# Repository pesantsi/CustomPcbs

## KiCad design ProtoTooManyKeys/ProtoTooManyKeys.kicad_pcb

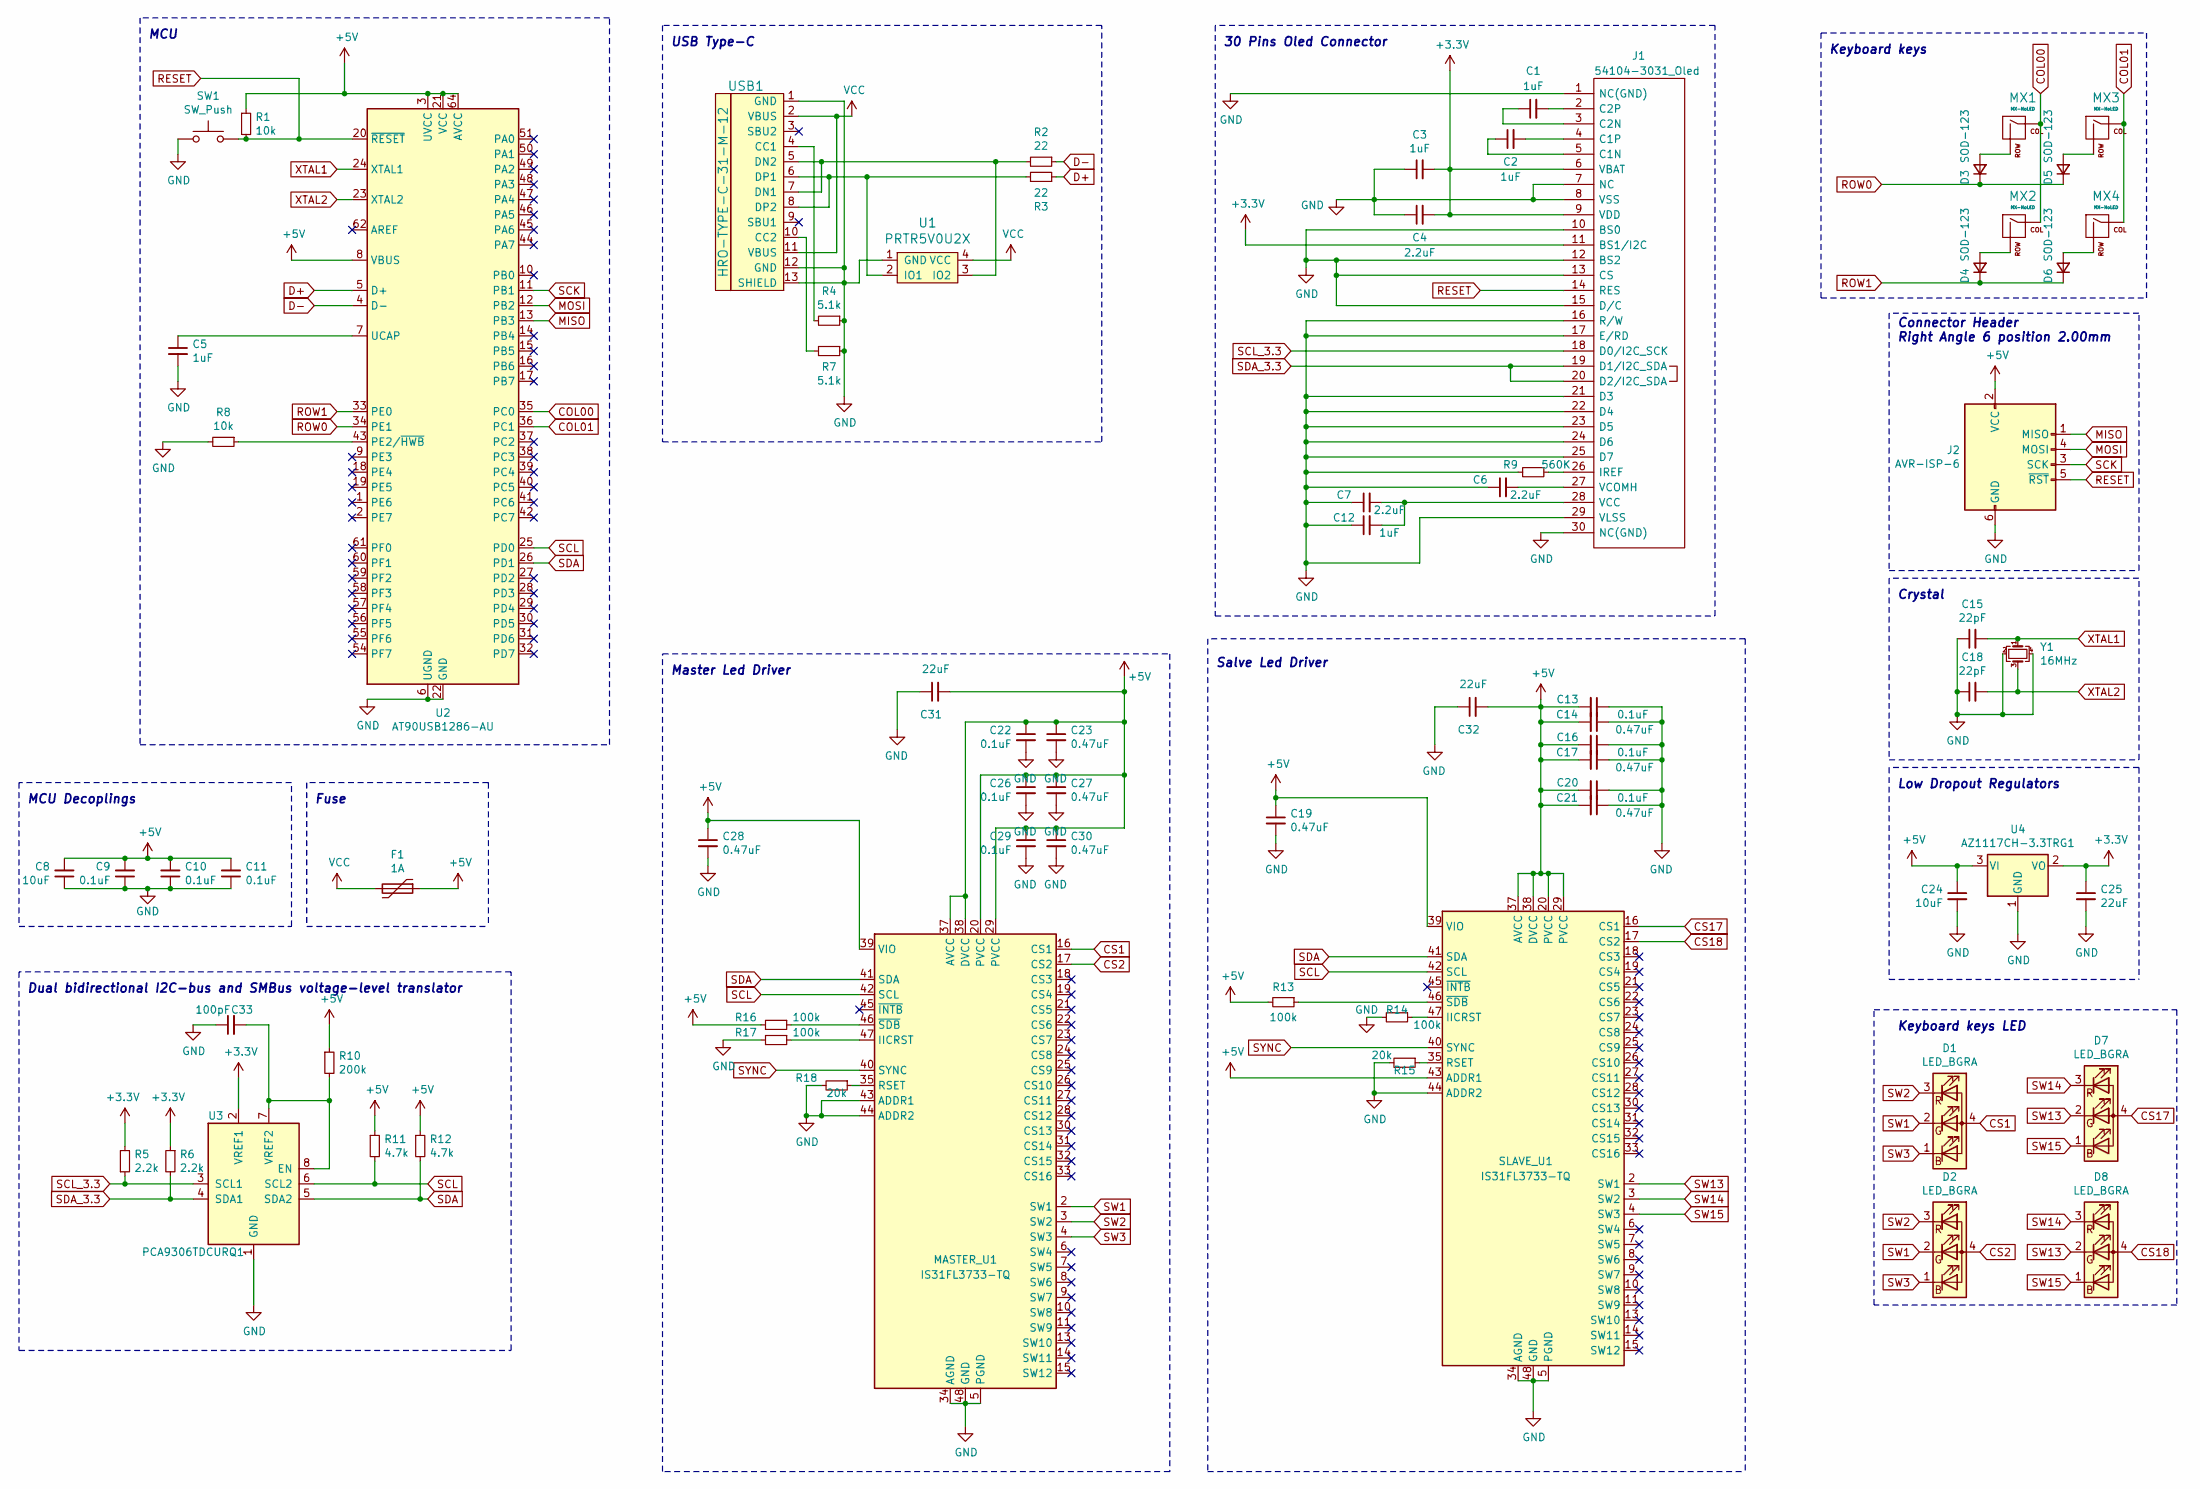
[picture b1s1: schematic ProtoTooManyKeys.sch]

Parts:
C1, C2, C3, C5, C12: 1uF; C_0805_2012Metric
C4, C6, C7: 2.2uF; C_0805_2012Metric
C8, C24: 10uF; C_0805_2012Metric
C9, C10, C11, C13, C16, C20, C22, C26, C29: 0.1uF; C_0805_2012Metric
C14, C17, C19, C21, C23, C27, C28, C30: 0.47uF; C_0805_2012Metric
C15, C18: 22pF; C_0805_2012Metric
C25, C31, C32: 22uF; C_0805_2012Metric
C33: 100pF; C_0805_2012Metric
D1, D2, D7, D8: LED_BGRA; QBLP677R-RGB
D3, D4, D5, D6: SOD-123; D_SOD-123
F1: 1A; Fuse_1206_3216Metric
J1: 54104-3031_Oled; 5051103091; Mouser Part Number 538-505110-3091
J2: AVR-ISP-6; SWR204NRTND03STGA
MASTER_U1: IS31FL3733-TQ; IS31FL3733-TQLS4
MX1, MX2, MX3, MX4: MX-NoLED; MXOnly-1U-NoLED_3Pins
R1, R8: 10k; R_0805_2012Metric
R2, R3: 22; R_0805_2012Metric
R4, R7: 5.1k; R_0805_2012Metric
R5, R6: 2.2k; R_0805_2012Metric
R9: 560K; R_0805_2012Metric
R10: 200k; R_0805_2012Metric
R11, R12: 4.7k; R_0805_2012Metric
R13, R14, R16, R17: 100k; R_0805_2012Metric
R15, R18: 20k; R_0805_2012Metric
SLAVE_U1: IS31FL3733-TQ; IS31FL3733-TQLS4
SW1: SW_Push; SKQG-1155865
U1: PRTR5V0U2X; SOT143B
U2: AT90USB1286-AU
U3: PCA9306TDCURQ1
U4: AZ1117CH-3.3TRG1; SOT-223-3_TabPin2
USB1: HRO-TYPE-C-31-M-12
Y1: 16MHz; Crystal_SMD_3225-4Pin_3.2x2.5mm

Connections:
+3V3: C3.2, C4.2, C25.1, J1.6 (VBAT), J1.9 (VDD), J1.11 (BS1/I2C), R5.2, R6.1, U3.2 (VREF1), U4.2 (VO)
+5V: C8.2, C9.2, C10.2, C11.2, C13.2, C14.2, C16.2, C17.2, C19.1, C20.2, C21.2, C22.1, C23.1, C24.1, C26.1, C27.1, C28.1, C29.1, C30.1, C31.2, C32.2, F1.1, J2.2 (VCC), MASTER_U1.20 (PVCC), MASTER_U1.29 (PVCC), MASTER_U1.37 (AVCC), MASTER_U1.38 (DVCC), MASTER_U1.39 (VIO), R1.1, R10.1, R11.1, R12.1, R13.2, R16.2, SLAVE_U1.20 (PVCC), SLAVE_U1.29 (PVCC), SLAVE_U1.37 (AVCC), SLAVE_U1.38 (DVCC), SLAVE_U1.39 (VIO), SLAVE_U1.43 (ADDR1), U2.3 (UVCC), U2.8 (VBUS), U2.21 (VCC), U2.52 (VCC), U2.64 (AVCC), U4.3 (VI)
COL00: MX1.1 (COL), MX2.1 (COL), U2.35 (PC0)
COL01: MX3.1 (COL), MX4.1 (COL), U2.36 (PC1)
CS1: D1.4 (A), MASTER_U1.16 (CS1)
CS2: D2.4 (A), MASTER_U1.17 (CS2)
CS17: D7.4 (A), SLAVE_U1.16 (CS1)
CS18: D8.4 (A), SLAVE_U1.17 (CS2)
D+: R3.1, U2.5 (D+)
D-: R2.1, U2.4 (D-)
GND: C3.1, C4.1, C5.2, C6.1, C7.1, C8.1, C9.1, C10.1, C11.1, C12.1, C13.1, C14.1, C15.1, C16.1, C17.1, C18.1, C19.2, C20.1, C21.1, C22.2, C23.2, C24.2, C25.2, C26.2, C27.2, C28.2, C29.2, C30.2, C31.1, C32.1, C33.1, J1.1 (NC(GND)), J1.7 (NC), J1.8 (VSS), J1.10 (BS0), J1.12 (BS2), J1.13 (CS), J1.15 (D/C), J1.16 (R/W), J1.17 (E/RD), J1.21 (D3), J1.22 (D4), J1.23 (D5), J1.24 (D6), J1.25 (D7), J1.29 (VLSS), J1.30 (NC(GND)), J2.6 (GND), MASTER_U1.5 (PGND), MASTER_U1.12 (PGND), MASTER_U1.34 (AGND), MASTER_U1.43 (ADDR1), MASTER_U1.44 (ADDR2), MASTER_U1.48 (GND), MASTER_U1.49 (GND), R4.1, R7.1, R8.2, R9.2, R14.2, R15.2, R17.2, R18.2, SLAVE_U1.5 (PGND), SLAVE_U1.12 (PGND), SLAVE_U1.34 (AGND), SLAVE_U1.44 (ADDR2), SLAVE_U1.48 (GND), SLAVE_U1.49 (GND), SW1.1, U1.1 (GND), U2.6 (UGND), U2.22 (GND), U2.53 (GND), U2.63 (GND), U3.1 (GND), U4.1 (GND), USB1.1 (GND), USB1.12 (GND), USB1.13 (SHIELD), Y1.2, Y1.4
MISO: J2.1 (MISO), U2.13 (PB3)
MOSI: J2.4 (MOSI), U2.12 (PB2)
unnamed: C1.1, J1.3 (C2N)
unnamed: C1.2, J1.2 (C2P)
unnamed: C2.1, J1.5 (C1N)
unnamed: C2.2, J1.4 (C1P)
unnamed: C5.1, U2.7 (UCAP)
unnamed: C6.2, J1.27 (VCOMH)
unnamed: C7.2, C12.2, J1.28 (VCC)
unnamed: C33.2, R10.2, U3.7 (VREF2), U3.8 (EN)
unnamed: D3.2 (A), MX1.2 (ROW)
unnamed: D4.2 (A), MX2.2 (ROW)
unnamed: D5.2 (A), MX3.2 (ROW)
unnamed: D6.2 (A), MX4.2 (ROW)
unnamed: J1.26 (IREF), R9.1
unnamed: MASTER_U1.35 (RSET), R18.1
unnamed: MASTER_U1.46 (~SDB), R16.1
unnamed: MASTER_U1.47 (IICRST), R17.1
unnamed: R2.2, U1.3 (IO2), USB1.5 (DN2), USB1.7 (DN1)
unnamed: R3.2, U1.2 (IO1), USB1.6 (DP1), USB1.8 (DP2)
unnamed: R4.2, USB1.4 (CC1)
unnamed: R7.2, USB1.10 (CC2)
unnamed: R8.1, U2.43 (PE2/~HWB)
unnamed: R13.1, SLAVE_U1.46 (~SDB)
unnamed: R14.1, SLAVE_U1.47 (IICRST)
unnamed: R15.1, SLAVE_U1.35 (RSET)
RESET: J1.14 (RES), J2.5 (~RST), R1.2, SW1.2, U2.20 (~RESET)
ROW0: D3.1 (K), D5.1 (K), U2.34 (PE1)
ROW1: D4.1 (K), D6.1 (K), U2.33 (PE0)
SCK: J2.3 (SCK), U2.11 (PB1)
SCL: MASTER_U1.42 (SCL), R11.2, SLAVE_U1.42 (SCL), U2.25 (PD0), U3.6 (SCL2)
SCL_3.3: J1.18 (D0/I2C_SCK), R5.1, U3.3 (SCL1)
SDA: MASTER_U1.41 (SDA), R12.2, SLAVE_U1.41 (SDA), U2.26 (PD1), U3.5 (SDA2)
SDA_3.3: J1.19 (D1/I2C_SDA), J1.20 (D2/I2C_SDA), R6.2, U3.4 (SDA1)
SW1: D1.2 (GK), D2.2 (GK), MASTER_U1.2 (SW1)
SW2: D1.3 (RK), D2.3 (RK), MASTER_U1.3 (SW2)
SW3: D1.1 (BK), D2.1 (BK), MASTER_U1.4 (SW3)
SW13: D7.2 (GK), D8.2 (GK), SLAVE_U1.2 (SW1)
SW14: D7.3 (RK), D8.3 (RK), SLAVE_U1.3 (SW2)
SW15: D7.1 (BK), D8.1 (BK), SLAVE_U1.4 (SW3)
SYNC: MASTER_U1.40 (SYNC), SLAVE_U1.40 (SYNC)
VCC: F1.2, U1.4 (VCC), USB1.2 (VBUS), USB1.11 (VBUS)
XTAL1: C15.2, U2.24 (XTAL1), Y1.1
XTAL2: C18.2, U2.23 (XTAL2), Y1.3

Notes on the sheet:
Dual bidirectional I2C-bus and SMBus voltage-level translator
Low Dropout Regulators
Crystal
MCU Decoplings
Fuse
Connector Header Right Angle 6 position 2.00mm
Master Led Driver
Salve Led Driver
30 Pins Oled Connector
USB Type-C
MCU
Keyboard keys
Keyboard keys LED

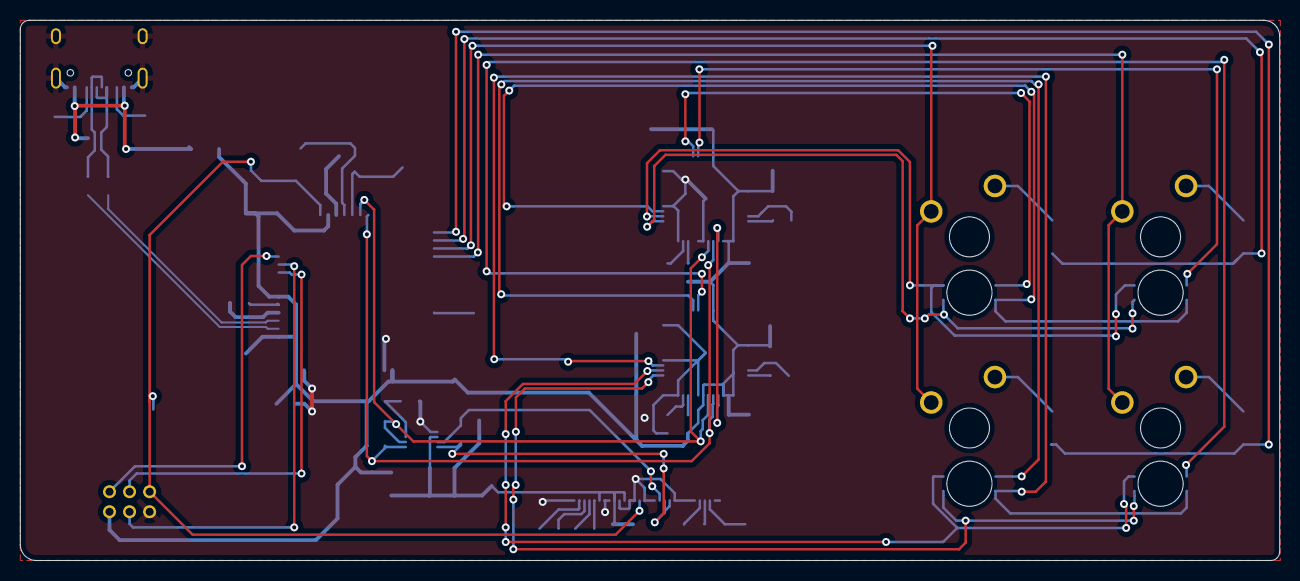
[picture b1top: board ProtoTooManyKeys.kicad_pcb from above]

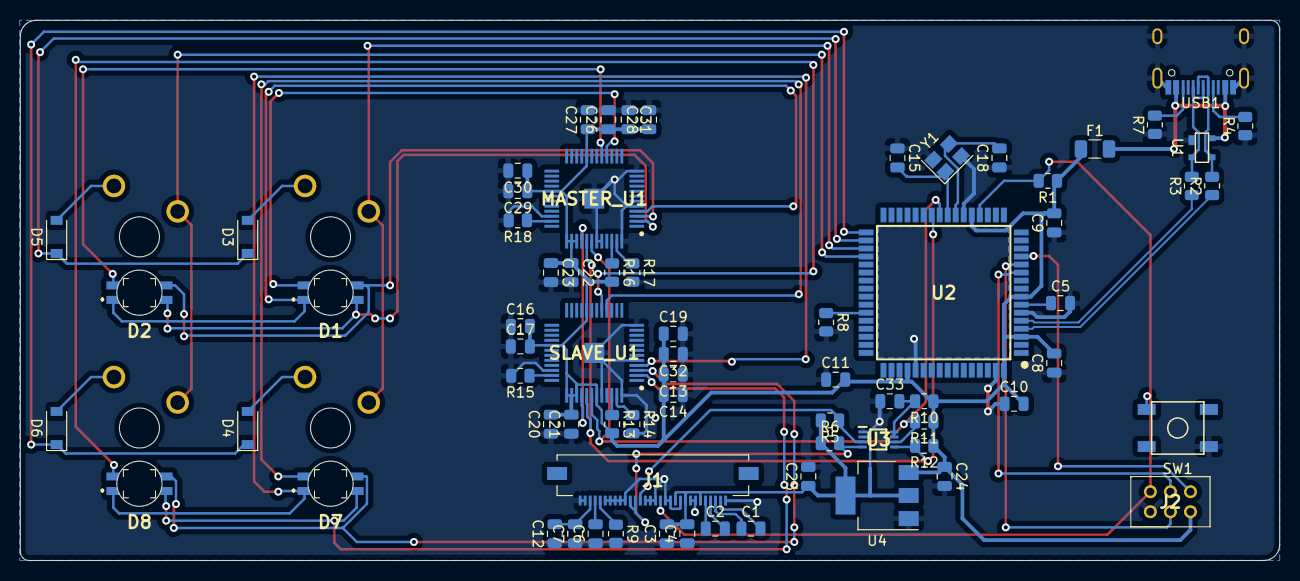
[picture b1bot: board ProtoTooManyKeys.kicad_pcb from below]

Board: 2 copper layers, 125.5 x 53.8 mm, 75 parts (71 on the bottom side), 55 nets.

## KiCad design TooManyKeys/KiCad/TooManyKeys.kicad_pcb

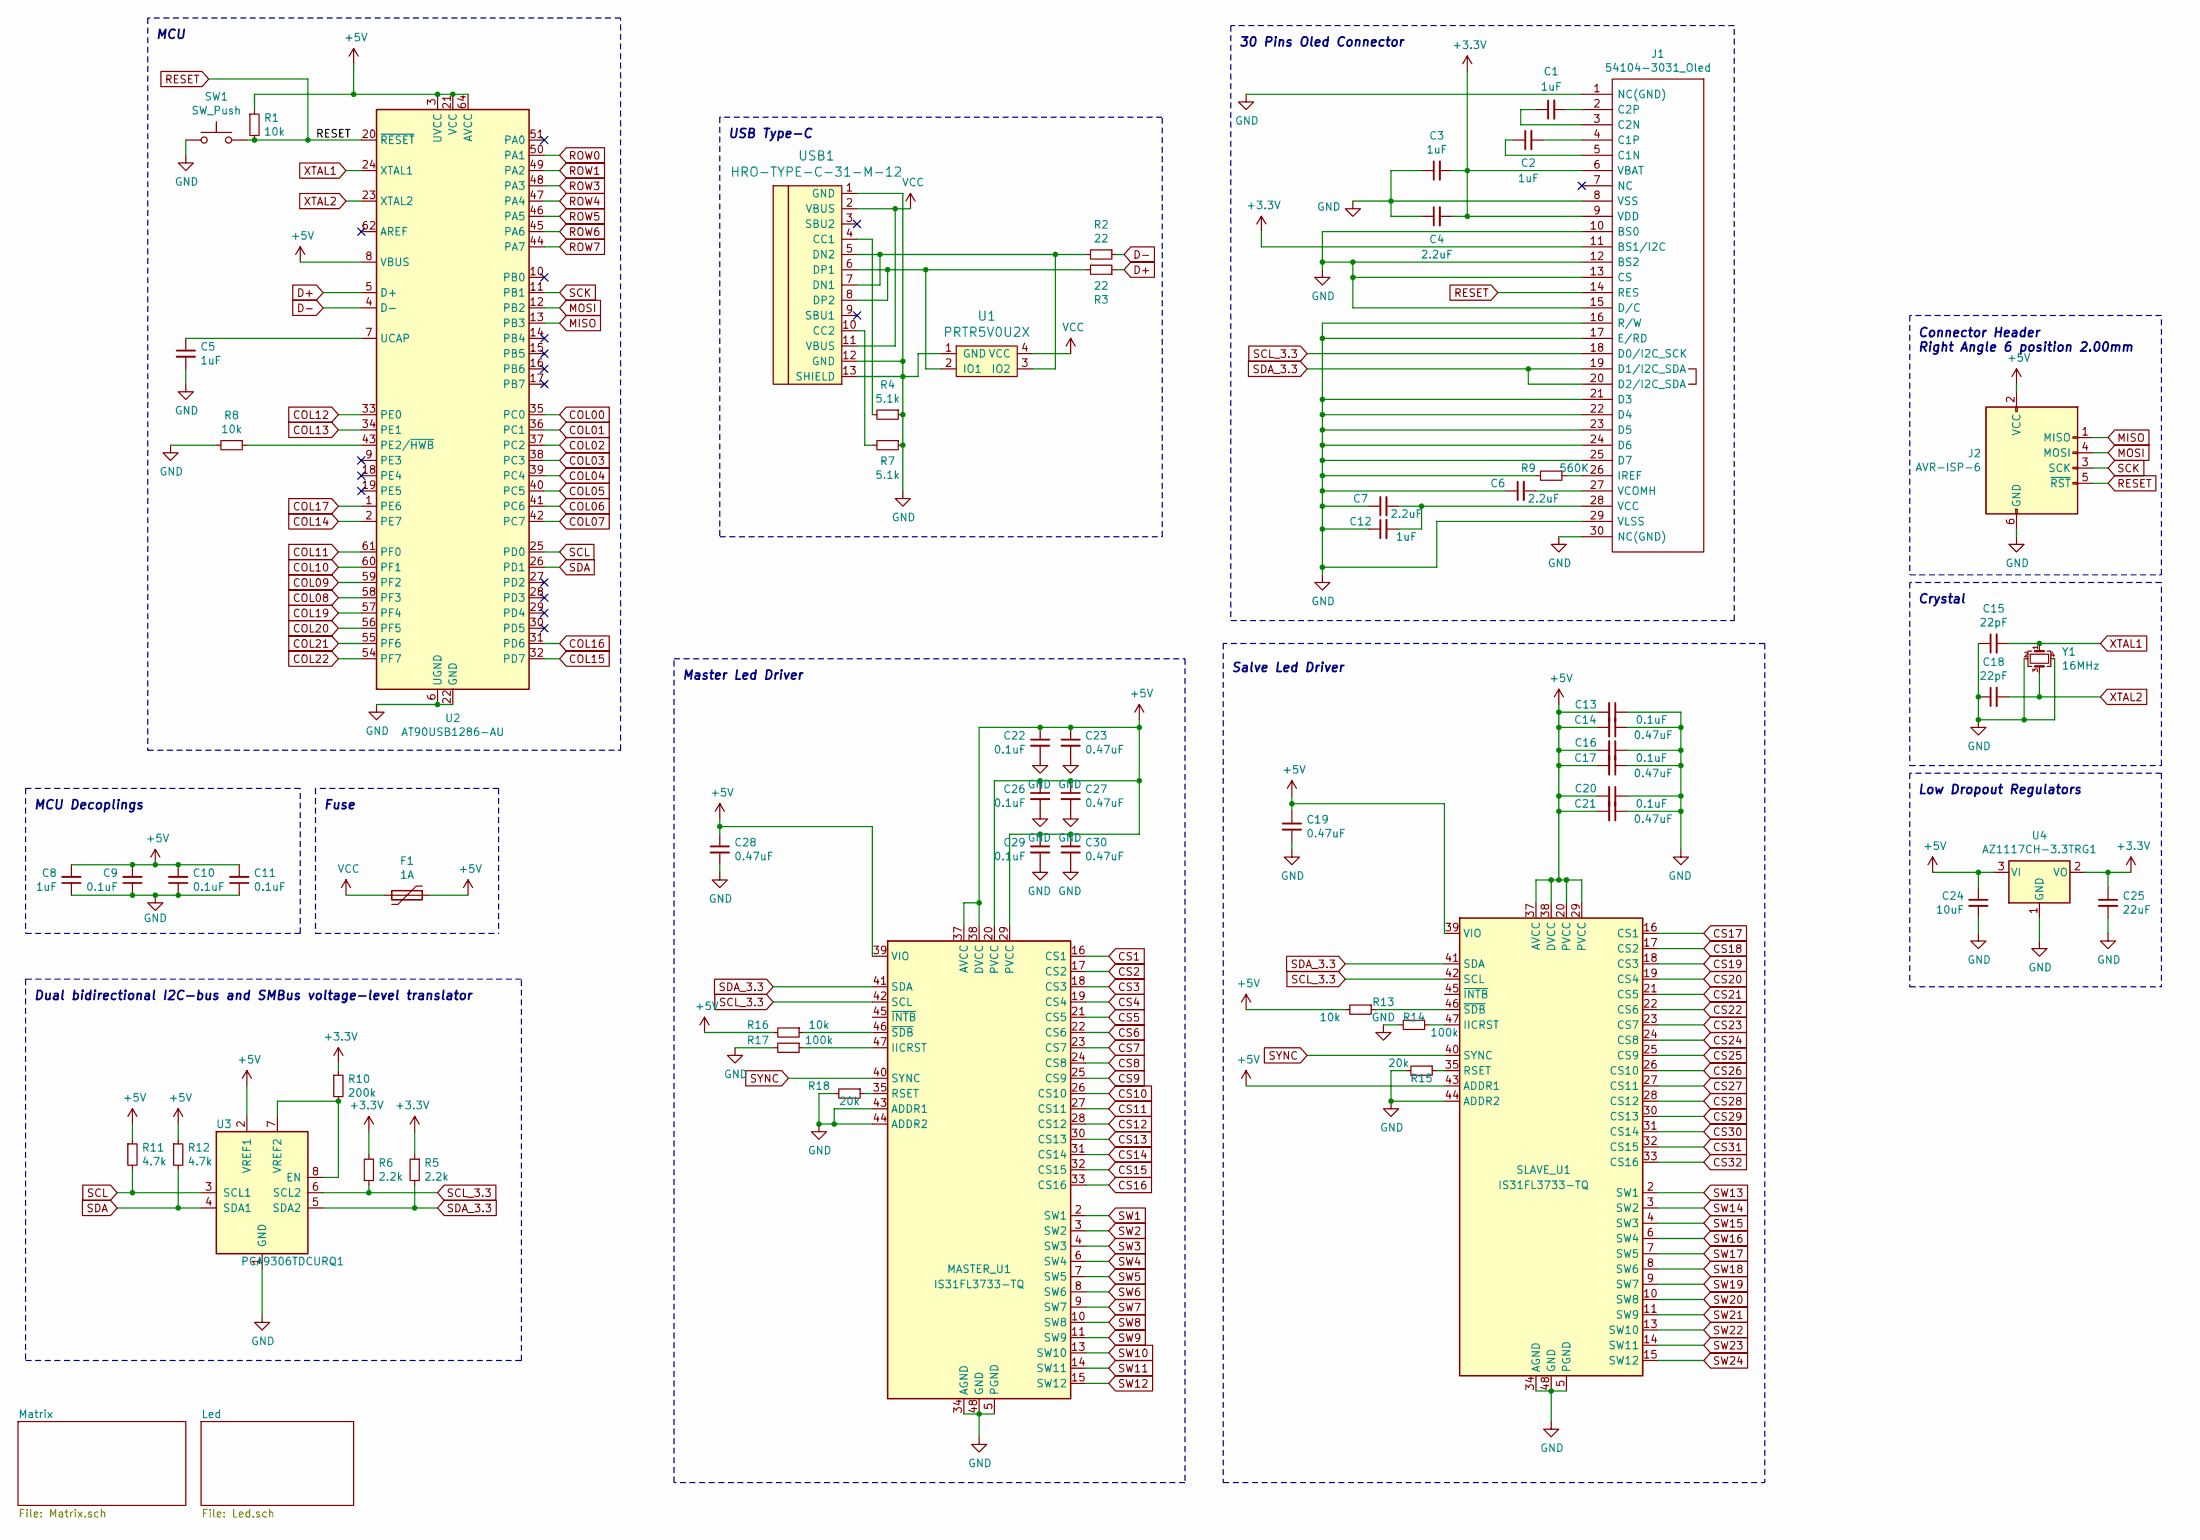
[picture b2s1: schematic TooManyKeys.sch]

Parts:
C1, C2, C3, C5, C8, C12: 1uF; C_0805_2012Metric
C4, C6, C7: 2.2uF; C_0805_2012Metric
C9, C10, C11, C13, C16, C20, C22, C26, C29: 0.1uF; C_0805_2012Metric
C14, C17, C19, C21, C23, C27, C28, C30: 0.47uF; C_0805_2012Metric
C15, C18: 22pF; C_0805_2012Metric
C24: 10uF; C_0805_2012Metric
C25: 22uF; C_0805_2012Metric
F1: 1A; Fuse_1206_3216Metric
J1: 54104-3031_Oled; 0541043033; Mouser Part Number 538-505110-3091
J2: AVR-ISP-6; SWR204NRTND03STGA
MASTER_U1: IS31FL3733-TQ; QFP50P900X900X120-49N
R1, R8, R13, R16: 10k; R_0805_2012Metric
R2, R3: 22; R_0805_2012Metric
R4, R7: 5.1k; R_0805_2012Metric
R5, R6: 2.2k; R_0805_2012Metric
R9: 560K; R_0805_2012Metric
R10: 200k; R_0805_2012Metric
R11, R12: 4.7k; R_0805_2012Metric
R14, R17: 100k; R_0805_2012Metric
R15, R18: 20k; R_0805_2012Metric
SLAVE_U1: IS31FL3733-TQ; QFP50P900X900X120-49N
SW1: SW_Push; SKQG-1155865
U1: PRTR5V0U2X; SOT143B
U2: AT90USB1286-AU; QFP80P1600X1600X120-64N
U3: PCA9306TDCURQ1; SOP50P310X90-8N
U4: AZ1117CH-3.3TRG1; SOT-223-3_TabPin2
USB1: HRO-TYPE-C-31-M-12
Y1: 16MHz; Crystal_SMD_3225-4Pin_3.2x2.5mm

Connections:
+3V3: C3.2, C4.2, C25.1, J1.6 (VBAT), J1.9 (VDD), J1.11 (BS1/I2C), R5.1, R6.2, R10.1, U4.2 (VO)
+5V: C8.2, C9.2, C10.2, C11.2, C13.2, C14.2, C16.2, C17.2, C19.1, C20.2, C21.2, C22.1, C23.1, C24.1, C26.1, C27.1, C28.1, C29.1, C30.1, F1.1, J2.2 (VCC), MASTER_U1.20 (PVCC), MASTER_U1.29 (PVCC), MASTER_U1.37 (AVCC), MASTER_U1.38 (DVCC), MASTER_U1.39 (VIO), R1.1, R11.1, R12.1, R13.2, R16.2, SLAVE_U1.20 (PVCC), SLAVE_U1.29 (PVCC), SLAVE_U1.37 (AVCC), SLAVE_U1.38 (DVCC), SLAVE_U1.39 (VIO), SLAVE_U1.43 (ADDR1), U2.3 (UVCC), U2.8 (VBUS), U2.21 (VCC), U2.52 (VCC), U2.64 (AVCC), U3.2 (VREF1), U4.3 (VI)
COL00: U2.35 (PC0); also elsewhere on the board
COL01: U2.36 (PC1); also elsewhere on the board
COL02: U2.37 (PC2); also elsewhere on the board
COL03: U2.38 (PC3); also elsewhere on the board
COL04: U2.39 (PC4); also elsewhere on the board
COL05: U2.40 (PC5); also elsewhere on the board
COL06: U2.41 (PC6); also elsewhere on the board
COL07: U2.42 (PC7); also elsewhere on the board
COL08: U2.58 (PF3); also elsewhere on the board
COL09: U2.59 (PF2); also elsewhere on the board
COL10: U2.60 (PF1); also elsewhere on the board
COL11: U2.61 (PF0); also elsewhere on the board
COL12: U2.33 (PE0); also elsewhere on the board
COL13: U2.34 (PE1); also elsewhere on the board
COL14: U2.2 (PE7); also elsewhere on the board
COL15: U2.32 (PD7); also elsewhere on the board
COL16: U2.31 (PD6); also elsewhere on the board
COL17: U2.1 (PE6); also elsewhere on the board
COL19: U2.57 (PF4); also elsewhere on the board
COL20: U2.56 (PF5); also elsewhere on the board
COL21: U2.55 (PF6); also elsewhere on the board
COL22: U2.54 (PF7); also elsewhere on the board
CS1: MASTER_U1.16 (CS1); also elsewhere on the board
CS2: MASTER_U1.17 (CS2); also elsewhere on the board
CS3: MASTER_U1.18 (CS3); also elsewhere on the board
CS4: MASTER_U1.19 (CS4); also elsewhere on the board
CS5: MASTER_U1.21 (CS5); also elsewhere on the board
CS6: MASTER_U1.22 (CS6); also elsewhere on the board
CS7: MASTER_U1.23 (CS7); also elsewhere on the board
CS8: MASTER_U1.24 (CS8); also elsewhere on the board
CS9: MASTER_U1.25 (CS9); also elsewhere on the board
CS10: MASTER_U1.26 (CS10); also elsewhere on the board
CS11: MASTER_U1.27 (CS11); also elsewhere on the board
CS12: MASTER_U1.28 (CS12); also elsewhere on the board
CS13: MASTER_U1.30 (CS13); also elsewhere on the board
CS14: MASTER_U1.31 (CS14); also elsewhere on the board
CS15: MASTER_U1.32 (CS15); also elsewhere on the board
CS16: MASTER_U1.33 (CS16); also elsewhere on the board
CS17: SLAVE_U1.16 (CS1); also elsewhere on the board
CS18: SLAVE_U1.17 (CS2); also elsewhere on the board
CS19: SLAVE_U1.18 (CS3); also elsewhere on the board
CS20: SLAVE_U1.19 (CS4); also elsewhere on the board
CS21: SLAVE_U1.21 (CS5); also elsewhere on the board
CS22: SLAVE_U1.22 (CS6); also elsewhere on the board
CS23: SLAVE_U1.23 (CS7); also elsewhere on the board
CS24: SLAVE_U1.24 (CS8); also elsewhere on the board
CS25: SLAVE_U1.25 (CS9); also elsewhere on the board
CS26: SLAVE_U1.26 (CS10); also elsewhere on the board
CS27: SLAVE_U1.27 (CS11); also elsewhere on the board
CS28: SLAVE_U1.28 (CS12); also elsewhere on the board
CS29: SLAVE_U1.30 (CS13); also elsewhere on the board
CS30: SLAVE_U1.31 (CS14); also elsewhere on the board
CS31: SLAVE_U1.32 (CS15); also elsewhere on the board
CS32: SLAVE_U1.33 (CS16); also elsewhere on the board
D+: R3.1, U2.5 (D+)
D-: R2.1, U2.4 (D-)
GND: C3.1, C4.1, C5.2, C6.1, C7.1, C8.1, C9.1, C10.1, C11.1, C12.1, C13.1, C14.1, C15.1, C16.1, C17.1, C18.1, C19.2, C20.1, C21.1, C22.2, C23.2, C24.2, C25.2, C26.2, C27.2, C28.2, C29.2, C30.2, J1.1 (NC(GND)), J1.8 (VSS), J1.10 (BS0), J1.12 (BS2), J1.13 (CS), J1.15 (D/C), J1.16 (R/W), J1.17 (E/RD), J1.21 (D3), J1.22 (D4), J1.23 (D5), J1.24 (D6), J1.25 (D7), J1.29 (VLSS), J1.30 (NC(GND)), J2.6 (GND), MASTER_U1.5 (PGND), MASTER_U1.12 (PGND), MASTER_U1.34 (AGND), MASTER_U1.43 (ADDR1), MASTER_U1.44 (ADDR2), MASTER_U1.48 (GND), MASTER_U1.49 (GND), R4.1, R7.1, R8.2, R9.2, R14.2, R15.2, R17.2, R18.2, SLAVE_U1.5 (PGND), SLAVE_U1.12 (PGND), SLAVE_U1.34 (AGND), SLAVE_U1.44 (ADDR2), SLAVE_U1.48 (GND), SLAVE_U1.49 (GND), SW1.1, U1.1 (GND), U2.6 (UGND), U2.22 (GND), U2.53 (GND), U2.63 (GND), U3.1 (GND), U4.1 (GND), USB1.1 (GND), USB1.12 (GND), USB1.13 (SHIELD), Y1.2, Y1.4
MISO: J2.1 (MISO), U2.13 (PB3)
MOSI: J2.4 (MOSI), U2.12 (PB2)
unnamed: C1.1, J1.3 (C2N)
unnamed: C1.2, J1.2 (C2P)
unnamed: C2.1, J1.5 (C1N)
unnamed: C2.2, J1.4 (C1P)
unnamed: C5.1, U2.7 (UCAP)
unnamed: C6.2, J1.27 (VCOMH)
unnamed: C7.2, C12.2, J1.28 (VCC)
unnamed: J1.26 (IREF), R9.1
unnamed: MASTER_U1.35 (RSET), R18.1
unnamed: MASTER_U1.46 (~SDB), R16.1
unnamed: MASTER_U1.47 (IICRST), R17.1
unnamed: R2.2, U1.3 (IO2), USB1.5 (DN2), USB1.7 (DN1)
unnamed: R3.2, U1.2 (IO1), USB1.6 (DP1), USB1.8 (DP2)
unnamed: R4.2, USB1.4 (CC1)
unnamed: R7.2, USB1.10 (CC2)
unnamed: R8.1, U2.43 (PE2/~HWB)
unnamed: R10.2, U3.7 (VREF2), U3.8 (EN)
unnamed: R13.1, SLAVE_U1.46 (~SDB)
unnamed: R14.1, SLAVE_U1.47 (IICRST)
unnamed: R15.1, SLAVE_U1.35 (RSET)
RESET: J1.14 (RES), J2.5 (~RST), R1.2, SW1.2, U2.20 (~RESET)
ROW0: U2.50 (PA1); also elsewhere on the board
ROW1: U2.49 (PA2); also elsewhere on the board
ROW3: U2.48 (PA3); also elsewhere on the board
ROW4: U2.47 (PA4); also elsewhere on the board
ROW5: U2.46 (PA5); also elsewhere on the board
ROW6: U2.45 (PA6); also elsewhere on the board
ROW7: U2.44 (PA7); also elsewhere on the board
SCK: J2.3 (SCK), U2.11 (PB1)
SCL: R11.2, U2.25 (PD0), U3.3 (SCL1)
SCL_3.3: J1.18 (D0/I2C_SCK), MASTER_U1.42 (SCL), R6.1, SLAVE_U1.42 (SCL), U3.6 (SCL2)
SDA: R12.2, U2.26 (PD1), U3.4 (SDA1)
SDA_3.3: J1.19 (D1/I2C_SDA), J1.20 (D2/I2C_SDA), MASTER_U1.41 (SDA), R5.2, SLAVE_U1.41 (SDA), U3.5 (SDA2)
SW1: MASTER_U1.2 (SW1); also elsewhere on the board
SW2: MASTER_U1.3 (SW2); also elsewhere on the board
SW3: MASTER_U1.4 (SW3); also elsewhere on the board
SW4: MASTER_U1.6 (SW4); also elsewhere on the board
SW5: MASTER_U1.7 (SW5); also elsewhere on the board
SW6: MASTER_U1.8 (SW6); also elsewhere on the board
SW7: MASTER_U1.9 (SW7); also elsewhere on the board
SW8: MASTER_U1.10 (SW8); also elsewhere on the board
SW9: MASTER_U1.11 (SW9); also elsewhere on the board
SW10: MASTER_U1.13 (SW10); also elsewhere on the board
SW11: MASTER_U1.14 (SW11); also elsewhere on the board
SW12: MASTER_U1.15 (SW12); also elsewhere on the board
SW13: SLAVE_U1.2 (SW1); also elsewhere on the board
SW14: SLAVE_U1.3 (SW2); also elsewhere on the board
SW15: SLAVE_U1.4 (SW3); also elsewhere on the board
SW16: SLAVE_U1.6 (SW4); also elsewhere on the board
SW17: SLAVE_U1.7 (SW5); also elsewhere on the board
SW18: SLAVE_U1.8 (SW6); also elsewhere on the board
SW19: SLAVE_U1.9 (SW7); also elsewhere on the board
SW20: SLAVE_U1.10 (SW8); also elsewhere on the board
SW21: SLAVE_U1.11 (SW9); also elsewhere on the board
SW22: SLAVE_U1.13 (SW10); also elsewhere on the board
SW23: SLAVE_U1.14 (SW11); also elsewhere on the board
SW24: SLAVE_U1.15 (SW12); also elsewhere on the board
SYNC: MASTER_U1.40 (SYNC), SLAVE_U1.40 (SYNC)
VCC: F1.2, U1.4 (VCC), USB1.2 (VBUS), USB1.11 (VBUS)
XTAL1: C15.2, U2.24 (XTAL1), Y1.1
XTAL2: C18.2, U2.23 (XTAL2), Y1.3

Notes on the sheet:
Dual bidirectional I2C-bus and SMBus voltage-level translator
Low Dropout Regulators
Crystal
MCU Decoplings
Fuse
Connector Header Right Angle 6 position 2.00mm
Master Led Driver
Salve Led Driver
30 Pins Oled Connector
USB Type-C
MCU
